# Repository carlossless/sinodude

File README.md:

# sinodude

A programming tool for SinoWealth 8051 microcontrollers.

## Warning

**This tool is experimental. Use at your own risk.**

SinoWealth microcontrollers have limited public documentation. This tool has been developed through reverse engineering and may not work correctly with all chip variants and all configurations.

## Supported Programmers

| Programmer | Description | Notes |
|------------|-------------|-------|
| sinodude-serial | Open-source Arduino Nano (ATmega328P or ATmega328PB) based programmer. See [firmware/README.md](firmware/README.md) for details. | Recommended |
| sinolink | The genuine SinoWealth SinoLink USB dongle (`258a:5063` / `258a:5007`), driven over WinUSB-style vendor control transfers plus bulk endpoints. | See the limitations below |

## Using the SinoLink dongle

Pick the backend with `-c sinolink` and the target power with `--power`:

| `--power` | effect |
|---|---|
| `3v3` (default) | dongle supplies 3.3 V |
| `5v` | dongle supplies 5 V |
| `external` | load switch stays off; the board powers the target |

The selection is checked against the part's `compatible_voltages` and then **verified against the
dongle's ADC**, so asking for 5 V on a 3.3 V-only part is refused and a rail that does not measure
what was asked for is an error rather than a silent overvolt.

```sh
sinodude read     -c sinolink -p sh68f90a --power 3v3 --flash out.hex
sinodude write    -c sinolink -p sh68f90a --power 5v  --flash firmware.hex
sinodude erase    -c sinolink -p sh68f90a --power 3v3
sinodude security -c sinolink -p sh68f90a --power 3v3 --write_protect 3
```

`sinodude sinolink` exposes the dongle directly for diagnostics, below the part abstraction:

```sh
sinodude sinolink probe
sinodude sinolink connect --part sh68f90a --power 3v3
sinodude sinolink dump    --part sh68f90a --power 3v3 --addr 0x1000 --len 0x40 --region custom
sinodude sinolink erase   --part sh68f90a --power 3v3 --erase_mode mass
sinodude sinolink program --part sh68f90a --power 3v3 --bin image.bin --addr 0
sinodude sinolink recover --part sh68f90a --power 3v3   # erase + restore upper options in one session
```

### Limitations

**The per-chip config blob is only solved for SH68F90A.** The dongle latches ChipType, the link
class, geometry and the region addresses from a 1 KiB blob the host downloads at connect. Deriving
that blob from a part's parameters is unfinished, so every other part gets the captured SH68F90A
blob with a handful of fields patched, and the driver warns when that happens. Symptom of a wrong
blob is a read that returns one uniform byte for the whole address space.

**Erased code flash reads `0x00` on SH68F90A, not `0xFF`.** Do not blank-check against `0xFF`.

**Mass erase clears the code options.** It takes the whole part with it, including the boot region
and the custom/option region, so the options have to be written back afterwards. The `write`
subcommand does this for you: it snapshots the custom region before erasing and restores it as part
of the write.

**Program code options with `sinolink options`, never with a raw write.** The code options live in
the custom region, but writing them there with an ordinary program request only sets the bits the
chip lets you set; the rest silently refuse and the operation reports `0xcc`. `bRequest 0x11`
(`sinodude sinolink options`) stages them out of the config blob instead and sets every bit,
including the ones a raw write cannot.

**Result `0xcc` means the write did not verify**, not "transient, retry". The dongle programs, reads
back, and reports `0xcc` on a mismatch. Treat it as a refused write.

**The dongle wedges, and a wedged dongle lies to you.** After enough operations it starts failing
everything: `0x09` on connect, `0xcc` on every write, long chunked reads that disagree between runs.
None of that means the target is broken. Power-cycle the dongle's USB port and it comes back:

```sh
uhubctl -l <hub> -p <port> -a cycle -d 2      # find it with: uhubctl | grep 258a
```

Cycle it before trusting any negative result, and between long write sequences. Several findings in
this file had to be re-verified on a freshly cycled dongle before they could be believed.

**The custom page at `0x1000` holds several different fields; do not write it blind.** On an
SH68F90A the layout is CustomerID at `0x1000`, OperationNumber at `0x1004`, CustomerOption at
`0x1006` and the **security/protection record at `0x100a`**. Writing a 16-byte block at `0x1000`
therefore writes the protection record too. Bytes put there decode as per-group protection: writing
`0f 00 00 88` at `0x100a` marks group 0 protected, which shows up as a program failing at address 1,
and `00 00 00 88` marks groups 6 and 7.

Protection only takes effect with the flag byte `0x33` at record offset `0x10` plus the 6-byte mark,
so stray bits in the record decode as protected without actually blocking writes. Use the
`security` subcommand to check what is really in there.

**Writing the `0x1000` page erases code flash `0x0000-0x0fff`** as a side effect, verified with a
dongle power cycle between write and read. So write custom fields **before** the flash image, never
after. The `write` subcommand already orders it that way.

Mass erase clears the whole page, protection record included, so re-write what you need after any
erase-and-program cycle.

**Do not read immediately after a write.** The dongle answers from a stale internal buffer: a full
dump taken right after an option write returned the option bytes at address 0. The driver settles
for 20 ms after programming and after connecting, which was enough to make repeated full-flash
dumps byte-identical, but a verify pass is still worth doing in a separate session.

### Restore the upper code options in the same session as the erase

Code options are eight bytes: 0-3 at `CustomerOption` (`0x1006` on an SH68F90A) and 4-7 at a fixed
`0x1100`, both in the custom region. Byte 7 holds `OP_ISPSIZE` in its high nibble and
`OP_EEPROMSIZE` in its low nibble, inverse-coded so `8` means "reserve nothing". `SH68F90A.GPT`
gives `[EEPROM] 0`, `[ISPSIZE] 0` and `default_code_options[7] = 0x88`, so the whole 64 KiB is code
flash.

**Mass erase clears that page, and if byte 7 comes back `0x00` the part reserves 8 KiB of ISP plus
4 KiB of EEPROM and refuses to program above `0xd000`.** Erase therefore has to put the upper
options back, and this is the part that bites:

> The upper option page is only writable in the ICP session the erase leaves open. Reconnect first
> and the write fails with `0xcc` and nothing lands, every time. `mass_erase_with_mode` restores
> the options before it reconnects, mirroring `blank_security_and_set_code_option_defaults` in
> sinodude-serial, which is called from inside `mass_erase()` for the same reason.

Symptoms of getting this wrong: programming stops at `0xd000` with `0xcc`, the option page at
`0x1100` refuses writes at offset 3 while offsets 0, 1, 2 and 4 take, and the custom space behaves
oddly because the carve-out is live. All of it clears up once byte 7 reads `0x88`.

Two traps while debugging this. Writing **zeros** "succeeds" anywhere, because the echo of an erased
cell already matches, so a zero-fill probe proves nothing. And a **read taken soon after a write**
can return the dongle's stale buffer, so a program-then-verify inside one session can report success
for a region that was never written; power-cycle the dongle before trusting a negative result.

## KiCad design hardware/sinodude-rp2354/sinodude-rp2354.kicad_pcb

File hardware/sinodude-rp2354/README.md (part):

# sinodude-rp2354

A USB ICP programmer for SinoWealth 8051 microcontrollers, built on an RP2354A.

The target-facing side is switchable between 3.3 V and 5 V, level-translated, and can be
actively discharged, so the host can power-cycle a target cleanly. That matters: SinoWealth
parts only enter ICP mode on a power-on sequence, and a target rail that decays slowly
through its own decoupling will not re-trigger it.

The probe header is pin-compatible with the SinoWealth SinoLink V2.2, so existing cables
and adapters work unchanged.

## Status

| | |
|---|---|
| Schematic | complete — 93 components, ERC clean |
| Sourcing | 88 of 93 parts carry an `LCSC` field; the 5 without are mounting holes and Tag-Connect pads |
| PCB | complete — 64 × 36 mm, two layers, fully routed, DRC clean |

## Sourcing

Every component has a footprint. LCSC part numbers are in an `LCSC` field on each symbol,
picked from the JLCPCB catalogue, preferring Basic/Preferred parts where one exists.

**The same field has to exist on the board's footprints, not only on the symbols.** The
Fabrication Toolkit is a pcbnew plugin: it reads footprint fields and knows nothing about
the schematic. With the field only on the symbols its BOM comes out with an empty
`LCSC Part #` column, JLCPCB falls back to guessing from the comment and footprint, and the
guesses are wrong in the expensive direction — it matched `RESET` to a reset switch and
`USB-C` to a different receptacle, and gave up entirely on the diodes, ferrite, inductor and
DUT header. All 88 footprints carry the field now. If you add a part, put `LCSC` on the
symbol *and* make sure it reaches the board.

### Value fields carry the binding spec

Parts whose datasheet imposes a real constraint spell it out in the Value field, Olimex
style, so the requirement travels with the symbol instead of living only in this README:

```
L1   3.3uH/20%/Isat2.4A/DCR140m/POL      C22,C23  15pF/50V/5%/C0G/C0603
C19  10uF/10V/10%/X5R/C0603              R15      750R/1%/ILIM333mA
C20,C21,C37  4.7uF/16V/10%/X5R/C0603     R21      150R/1%/250mW/R1206
R5   33R/1%/R0603                        F1       750mA/Rmax290mR/F1206
Y1   12MHz/CL10pF/ESR50R/ABM8-272-T3      D4-D9    H5VSD3B/VRWM5V/SOD-323
```

Generic 10 k / 100 nF parts keep plain values — stamping specs on those only fragments the
BOM without protecting anything.

### Core regulator parts, against RP2350 datasheet §6.3.8

The datasheet opens that section with *"this should be placed first on any board design and
these guidelines must be strictly followed"*, and gives hard numbers. What is fitted:

| Requirement | Part | Margin |
|---|---|---|
| L: shielded, 3.3 µH ±20%, DCR ≤ 250 mΩ, I_sat ≥ 1.5 A, polarity-marked | AOTA-B201610S3R3-101-T (`C42411119`) | DCR 140 mΩ max, I_sat 2.4 A min ✓ |
| C_OUT: 4.7 µF ±20%, ESR ≤ 250 mΩ, ESL ≤ 6 nH | C21, 0603 4.7 µF 16 V X5R ±10% (`C19666`) | on 1.1 V, so negligible DC-bias loss |
| C_IN: ≥ 4.7 µF, ESR ≤ 50 mΩ | C19, 0603 **10 µF** 10 V X5R (`C19702`) | 10 µF chosen because a 4.7 µF part derates below the floor at 3.3 V bias |
| Second 4.7 µF on V_OUT at a DVDD pin, away from L1/C21 | C37 (`C19666`) | recommended, not mandatory |

**C37 must not sit beside C21.** Parallel to C_OUT it simply doubles the 4.7 µF the
regulator is compensated for, and it picks up the LX node's switching edges. The datasheet
names DVDD pin 23 (QFN-60) as the place for it, but the escapes fanning north out of pins
21-27 leave no corridor there. C37 therefore sits west of U1 on DVDD pin 39, the same
supply: 4.0 mm from the pin and 12.5 mm of copper away from C21.

The inductor's polarity marking is functional, not cosmetic: the datasheet says leakage field
couples into the LX→L→C_OUT loop and affects the control loop and output voltage, which is
why Raspberry Pi had Abracon make a marked part. L1's footprint puts the dot on pad 1, which
must face VREG_LX.

L1 and C21 can only be deleted by powering DVDD from an external 1.1 V supply, disabling the
on-chip regulator and tying VREG_FB to ground — which costs a whole extra regulator, so it is
not worth it here. VREG_AVDD and VREG_VIN still need power in that case regardless, as they
run the power-on reset and brown-out detector.

**U3 (TPS2114A) is `C118265`, listed but currently at zero stock.** It is orderable rather
than absent, and at $1.92 it is the cheapest of its family. TI lists the part ACTIVE. The
only consequence is scheduling: a zero-stock part cannot come off JLCPCB's shelf for
assembly, so it has to be ordered against LCSC lead time or consigned.

**Do not substitute the TPS2115A for it.** The two share a datasheet and a pinout, and
differ in exactly three ways: current-limit range (0.31–0.75 A vs 0.63–2 A), the ILIM
constant (250 vs 500), and r_DS(on) (120 mΩ vs 84 mΩ). Our 333 mA sits mid-range for the
'2114A and *below the bottom* of the '2115A's, where the datasheet notes the minimum is set
"based on accuracy considerations" — i.e. the limit is not characterised there. Getting
333 mA from a '2115A needs R15 = 1.5 kΩ, outside its range; staying inside its range means
≥630 mA to the target, which breaks the 500 mA USB budget. R15's value is bound to the part
choice, which is why its Value field reads `750R/1%/ILIM333mA`.

Left without an LCSC — neither is a part:

| Ref | Why |
|---|---|
| H1–H4 | mounting holes, drilled features rather than components |
| J2 | Tag-Connect TC2030 is bare pads — the pogo cable touches copper |

Every part that is physically placed on the board has an LCSC number. J1, J4, SW1 and SW2
all resolved to exact matches for the footprints already drawn:

| Ref | Part | LCSC | Note |
|---|---|---|---|
| J1 | GCT USB4105-GF-A-120 | `C5184243` | swapped from the HCTL part, see below |
| J4 | ZHOURI DC3-2.54-10PAL | `C5156674` | right-angle shrouded box header |
| SW1, SW2 | C&K KMR221GLFS | `C72443` | the part the KiCad footprint is named after |

**Watch the DC3 suffix when reordering J4.** The family splits on one letter: `-10PAS` is
`Plugin`, i.e. vertical, and `-10PAL` is `Push-Pull`, i.e. **Right Angle**. Only the PAL
fits `IDC-Header_2x05_P2.54mm_Horizontal`. Ordering the PAS gives you a connector that
physically fits the same holes but points the cable straight up off the board.

**U2 is now an AMS1117-3.3** (`C6186`, Basic, ~1.4 M in stock), not the NCP1117 the RP2350
guide uses — NCP1117 is not stocked at JLCPCB. Same SOT-223 land pattern, same pinout
(1 GND, 2 VO, 3 VI).

One part-choice consequence worth knowing:

- **C27 (10 µF on VTGT) slows supply switching.** The TPS211xA will not connect a supply
  until OUT has fallen within 100 mV of it, so on a 5 V → 3.3 V change VTGT must decay to
  ~3.4 V first. TI notes the fast input-to-input slew "reduces the output voltage hold-up
  capacitance requirement". Q1 is therefore not optional for voltage changes, not just for
  ICP power cycling — or drop C27 to 1–4.7 µF.

### 3D models

Every footprint representing a physical part resolves a 3D model — 88 of the 93. The five
without are the Tag-Connect pad pattern and the four mounting holes, none of which is a
component.

Check it with `kicad-cli pcb export step`, not by eye. A footprint can carry a model in the
library and still have none on the board, because the board keeps its own copy of the
footprint; U1 sat like that for a while, model file present, library entry present, board
instance empty.

`flake.nix` exports `KICAD10_3DMODEL_DIR` — without it none of the stock models resolve at
all, since every footprint references that variable.

Two models are generated locally into `3dmodels/`, because the KiCad library ships neither:

| Model | Why |
|---|---|
| `QFN-60-1EP_7x7mm_P0.4mm_EP3.4x3.4mm.step` | the KiCad 3D library has QFN-52 and QFN-56 in 7×7 but **no QFN-60**, so the RP2354A had no body at all |
| `L_Abracon_AOTA-B201610S_0806_2016Metric.step` | matches the custom inductor footprint |

Both were built in FreeCAD to datasheet nominals — the QFN to RP2350 datasheet Figure 143
(D/E 7 BSC, A 0.85, A1 0.02, A3 0.203 REF, D2/E2 3.40, b 0.18, e 0.400 BSC, L 0.40) and the
inductor to Abracon's 2.00 × 1.60 × 1.00 max. Verified bounding boxes are 7.000 × 7.000 ×
0.850 and 2.000 × 1.600 × 1.000, origin centred, seating plane at z=0.

Each is exported as separate solids so it can carry per-solid STEP colour, using the same
three RGB values the stock KiCad models use (body `0.148/0.145/0.145`, leads and terminals
`0.824/0.820/0.781`, pin-1 and polarity marking `0.691/0.664/0.598`). Without that a
generated model renders flat grey next to every other part on the board.

They are visual and mechanical-fit models, not vendor CAD: lead geometry is nominal and
there is no internal detail. Good enough for enclosure fit and collision checks; if you need
certified geometry, replace them with vendor STEP.

Because a 3D model is attached to a footprint, `QFN-60-…_ThermalVias` is **copied** into
`footprints/sinodude.pretty` with its model path retargeted. Its nine thermal vias are also
widened from 0.5/0.2 mm to 0.6/0.3 mm, which is JLCPCB's minimum drill.

`footprints/sinodude.pretty` holds two more project copies, each because the stock footprint
does not fit this board:

| Footprint | Change |
|---|---|
| `USB_C_Receptacle_GCT_USB4105-xx-A_16P_TopMnt_Horizontal` | the four corner ground pads are 1.00 mm tall instead of 1.15 mm, so they clear the receptacle's own shell holes at a 0.25 mm hole-to-copper rule |
| `IDC-Header_2x05_P2.54mm_Horizontal` | the pin 1 arrow is shortened so it does not sit on R26's pad, and the body outline is clipped at the board edge it overhangs |

Copies do not pick up upstream library fixes. The trade is deliberate: with them, every
footprint on the board matches its library and DRC's library check is silent, so a real
drift will show up.

**J1 moved to the GCT USB4105** (`C5184243`, USB4105-GF-A-**120**, 16P, 4143 in stock). The
HCTL footprint referenced a model the library does not ship. GCT has an identical pad set
(A1 A4–A9 A12, B1 B4–B9 B12, SH), so this was a footprint swap with no schematic change, and
it does have a model. Note the `-120` suffix: the plain `USB4105-GF-A` and `-060` are 12-pin
parts and will not fit.

### Known items

- **The ERC pin matrix allows a bidirectional pin on a power-output net.** U4's unused pins
  (7–10 = A5–A8, 14–17 = B5–B8) are tied to GND, and GND carries a PWR_FLAG, so the stock
  matrix flags "bidirectional pin connected to power output" eight times. The wiring is
  right and KiCad only sees the pin *type*; it cannot know DIR is strapped. Rather than
  carry eight standing warnings, the Bidirectional × Power-output cell is set to "no
  warning" in the project's ERC matrix. ERC is clean; if you add a real bidirectional pin
  to a driven rail, that pair will no longer be caught for you.

  **Why both ports are grounded, not just the A side.** The SN74LVC8T245 datasheet §8.1 says
  *"It is recommended to tie all unused I/Os to GND. The device should not have any floating
  I/Os when changing translation direction"*, and the overview is blunter: *"The input
  circuitry on both A and B ports is always active and must have a logic HIGH or LOW level
  applied to prevent excess ICC and ICCZ."* The input receiver stays powered on a pin even
  while that pin is driven as an output, so a floating B pin still presents a floating CMOS
  input internally and still burns ICC. Every A and B pin is typed `I/O` in the pin table,
  not "output".

  Grounding an output is only safe because **DIR is hardwired to VCCA**, so the A→B direction
  never changes and B5–B8 sit driving low into GND — no contention, no current. If DIR ever
  became firmware-driven, both sides would need series resistors instead of hard ties. There
  is a note on the sheet saying so.
- **Schematic style follows Olimex.** Ten titled blocks, each boxed with dashed graphic lines
  (`polyline` notes lines, the same construct Olimex uses). Related parts sit next to each
  other and are joined with real wires; KiCad power symbols carry every rail; global labels
  are used only for signals that cross from one block to another.
- **`VTGT`, `ADC_AVDD` and `VREG_AVDD` are real power symbols**, not labels. KiCad takes a
  power symbol's net name from its Value field, so these are stock symbols (`power:VCC`,
  `power:+3.3VA`) with the Value overridden. Keep the Value if you copy them.
- **D1 is wired as a pass-through**, not as a shunt with its two I/O1 pins tied together.
  D+/D- enter one side of the USBLC6 and leave the other, so the signal runs through the
  diode pads rather than past them on a stub. That is ST's application circuit and gives the
  clamp a proper current path — but it does mean **D1 cannot be left unpopulated**.
- **`TDA` (header pin 7) is the Andes AICE data wire**, not an 8051 signal. SinoWealth's
  tool-selection note tabulates the adapter signals per target core: ARM gets SWD
  (`VDD SWCLK SWDIO GND`), Andes gets AICE (`VDD TCK TDA GND`), and the 8051 parts get
  `VDD TCK TDI TDO GND`. The 2x5 header carries both styles at once, so TDA shares TCK with
  the 8051 path and is otherwise unused until an Andes-core target is supported. It gets its
  own translator with a live DIR so firmware can drive it either way, and its passives now
  match the other target lines exactly: D9 clamp, 22 R series (R32), 10 k pull-up to `VTGT`
  (R33).

  An earlier revision gave pin 7 a 330 R series resistor and a fitted 100 nF, copied from
  what was taken to be SinoLink's equivalent net. Neither is on SinoLink's TDA: its cap
  position (C28) carries the value `DNI` and is not fitted, and the only 330 R on that sheet
  is a transistor-switched pull-up on **TDO**, a different pin. Together they made a 33 us
  low-pass on a wire whose whole protocol is edge timing. The cap is gone and D9 sits on its
  footprint, which also closes the gap where pin 7 was the only target signal with no clamp.
- **U1 uses the ThermalVias QFN footprint** (vias under the exposed pad). The project copy
  drills them at 0.3 mm rather than the stock 0.2 mm, so they are inside JLCPCB's standard
  capability; if you retarget to a fab with a finer drill there is nothing to change.
- **GPIO17–25 and 27–29 are unused** and carry no-connect flags. They are free if a later
  revision wants a header or a second target interface.
- **Both board edges are cut back from where the footprints put them**, so the connectors
  reach through a case wall. The GCT footprint's `PCB Edge` line on `Dwgs.User` sits flush
  with the receptacle's mating face; the Edge.Cuts line is 1.4 mm inboard of it. J4 gets the
  same treatment at the other end. If you ever move J1 or J4, the edges move with them.
- **F1 is a 750 mA part, not 500 mA.** Worst case through it is U3's target limit plus the
  board's own draw. The limit is not the 333 mA typical: scaling the datasheet's 700 Ω row
  (0.30 / 0.36 / 0.50 A) to R15 = 750 Ω gives **280 / 336 / 467 mA**, so worst case is
  ~540 mA. Against a 500 mA hold that is under 20%
  margin before derating, and PPTC hold current falls with ambient while U2 sits beside it
  burning ~0.7 W at that current, so it would nuisance-trip. The fitted part is now
  Littelfuse `1206L075/16WR` (`C371166`): 750 mA hold, 1.5 A trip, 90 mΩ typical and 290 mΩ
  after a trip, in the same 1206 land. Note the stock — about 6 k against 300 k for the
  500 mA Jinrui part it replaced. F1 guards the host port against a board fault; the
  target's own overcurrent limit is U3, so raising F1 does not weaken that.

  A **TI TPD3S014** (`C87384`, SOT-23-6) was weighed and turned down. It would replace both
  F1 and D1 with one part, limit electronically at a guaranteed 0.67 A rather than tripping
  thermally, and drop 42–56 mV instead of up to 125 mV — but it costs about a dollar more
  per board against two commodity parts, it is an Extended part at JLCPCB, and its 0.5 A
  continuous rating leaves only 14% over our worst case. Glasgow revC3 does use one, with no
  polyfuse at all. Do not reach for the TPD3S**044** if you revisit this: its limit is
  guaranteed only above 1.60 A, so a fault would pull more than a 500 mA host allows before
  it acted.
- **TPS2114A is old but not end-of-life.** TI lists both the TPS2114A and TPS2115A as
  ACTIVE — in production and recommended for new designs. The problem is purely that JLCPCB
  does not carry it, so it is a distributor question, not a lifecycle one: buy it from
  Digi-Key or Mouser and the part is fine.

## Board sections

```
      USB-C          power         RP2354A       translators      DUT 2x5
   ┌──────────┬────────────────┬──────────────┬──────────────┬────────────┐
   │ J1 D1 F1 │ U2 3V3  U3 mux │ U1  Y1  L1   │ U4  U5  U6   │ J4 + 22R   │
   │          │ Q1 discharge   │ SW1 SW2  J2  │              │ + ESD      │
   └──────────┴────────────────┴──────────────┴──────────────┴────────────┘
```

Signal flows left to right. Everything right of the translators is referenced to `VTGT`;
everything left of them is 3.3 V. RP2354 GPIOs are not 5 V tolerant, so no target-facing
signal bypasses a translator.

## DUT header (J4) — SinoLink V2.2 pinout

```
 1 VTGT    2 TCK
 3 GND     4 TDI
 5 GND     6 TMS
 7 TDA     8 TDO / DATA
 9 nRST   10 GND
```

Pin 7 serves Andes-core targets (`VDD TCK TDA GND`); pins 4, 6, 8 and 9 serve the 8051 path
(`TDI TMS TDO nRST`). TCK and VTGT are common to both. The dongle's single-wire pulse-width
transport for 8051 parts runs on **TDO, pin 8**, not on TDA.

### Wire-protocol coverage

SinoLink runs four wire protocols across these ten pins. Every one of them needs the same
three things from the hardware: a driven clock, a line that can turn around, and a reset.

| protocol | target | signals | path here |
|---|---|---|---|
| protoA, JTAG bit-bang | 8051 | nRESET TCK TDI TMS, TDO in | U4 drives the first four, U5 turns TDO around |
| protoB, single-wire pulse-width | 8051 | TCK + one bidirectional data wire | U4 drives TCK, U5 turns pin 8 around |
| CMSIS-DAP SWD | ARM | SWCLK(=TCK) SWDIO(=TDO) nRESET | same pins, U5 turns SWDIO around |
| AICE | Andes | TCK + TDA | U4 drives TCK, U6 turns pin 7 around |

The three lines that have to reverse (TDO, TDA, and nothing else) each sit on their own
translator with a GPIO-controlled DIR. TCK, TDI, TMS and nRST never reverse in any of the
four, so they share U4 with its DIR strapped `A->B`; `XLAT_OE` still tri-states all four so
another probe can drive the header.

**Pull-up strength is the one place SinoLink's topology forces a choice.** It translates its
data wire with a PCA9306, a passive pass-FET that cannot drive high at all, so both sides
need pull-ups and it fits 1 kOhm on the MCU side plus a transistor-switched 330 Ohm on the
target side. Those resistors are its high-side driver, not a bus bias. The SN74LVC1T45 used
here is push-pull and drives high itself, so no switched pull-up is needed; what remains is
the released-line case, where the target drives open-drain and the pull-up alone sets the
rising edge. R31 and R33 are therefore **1 kOhm**, matching SinoLink's static value, for a
~30 ns edge into the ~30 pF a short ribbon presents rather than the ~300 ns a 10 kOhm would
give. R29 on nRST stays 10 kOhm: a reset line is not clocked and should not fight a target
that drives it.

**Target-referenced I/O** (SinoLink's third VREF setting, after 5 V and 3.3 V) needs no
extra parts: leave U3 in its reset state (`D1 = D0 = 1`, OUT Hi-Z), let the target feed pin
1, and `VTGT` — which *is* pin 1 — becomes the target's own rail. That is what the
translators take as VCCB, and `VTGT_SENSE` reads it back on ADC0.

## Target supply (U3, TPS2114A)

Truth table, in the datasheet's own `D1, D0` column order:

| D1 | D0 | OUT | Mode |
|----|----|-----|------|
| 1 | 1 | Hi-Z | **off, the reset default** via R13/R14 10 k pull-ups |
| 1 | 0 | IN1 | 5.0 V |
| 0 | 1 | IN1 or IN2 | auto, picks whichever input is higher |
| 0 | 0 | IN2 | 3.3 V |

Note the pin/bit order: GPIO11 drives D0 and GPIO12 drives D1, so the firmware word is
`(D1 << 1) | D0`. Writing `D1=0, D0=1` gets you auto-switching, not a hard 5 V select.

`STAT` (GPIO14) is a supply-source indicator, not a fault flag. It is open-drain and pulls
low both when IN1 is selected **and** when OUT is Hi-Z, so it only disambiguates against the
mode firmware commanded. It is Hi-Z only while IN2 is selected.

Current limit is `I = 250 / R_ILIM`; R15 = 750 Ω gives 333 mA, which keeps probe plus target
inside a plain USB 500 mA budget. The part is a **TPS2114A**, not the TPS2115A: the '2115A's
specified ILIM adjustment range starts at 0.63 A, so 333 mA is off the bottom of it and the
limit accuracy is unspecified there. The two are pin-, package- and datasheet-identical, and
the '2114A's constant is half, putting 333 mA mid-range.

There is no series Schottky, so the target sees the full rail. Expect roughly 0.2 V below
nominal under load: the polyfuse F1 contributes 0.1 V to 0.4 V depending on the part fitted,
the mux another ~40 mV at 333 mA.

`VTGT` is capped at **5.25 V**, USB 5 V at +5 %. The translators' VCCB abs-max is 5.5 V, but
the binding limit is the ESD suppressors D4–D9: the H5VSD3B is specified to VRWM = 5 V with
VBR(min) = 6.2 V, so above ~5.25 V its leakage is unspecified and the margin to the
breakdown knee gets thin. **An external target above 5.5 V destroys U4–U6.**

## Target discharge (Q1)

`VTGT` is pulled down through R21 (150 Ω, 1206) by Q1. At 5 V that is 167 mW into a 250 mW
part, so it is rated for continuous assertion, but it is meant to be pulsed. R20 (100 k)
holds the gate low so the FET stays off while the RP2354 is in reset and its GPIOs are
inputs.

## Indicators (D2, D3)

Both run from `+3V3` through 470 Ω into the GPIO, so the pin sinks and both are active-low.

**Do not size these by current.** The two LEDs are binned at different test currents, and
reading the LCSC catalogue line instead of the datasheet gets this backwards:

| | part | Iv (bin range) | Vf | at | efficacy |
|---|---|---|---|---|---|
| D2 green, 517 nm | `C7496818` | 160–230 mcd | 2.6–2.9 V | IF = 5 mA | 32–46 mcd/mA |
| D3 red, 625 nm | `C2286` | 145–300 mcd | 1.8–2.4 V | IF = 20 mA | 7.3–15 mcd/mA |

At their respective test points the green is three to four times more efficient per
milliamp, and both are 120° parts, so the mcd figures compare directly for perceived
brightness. That is why the green gets the same resistor as the red rather than a smaller
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
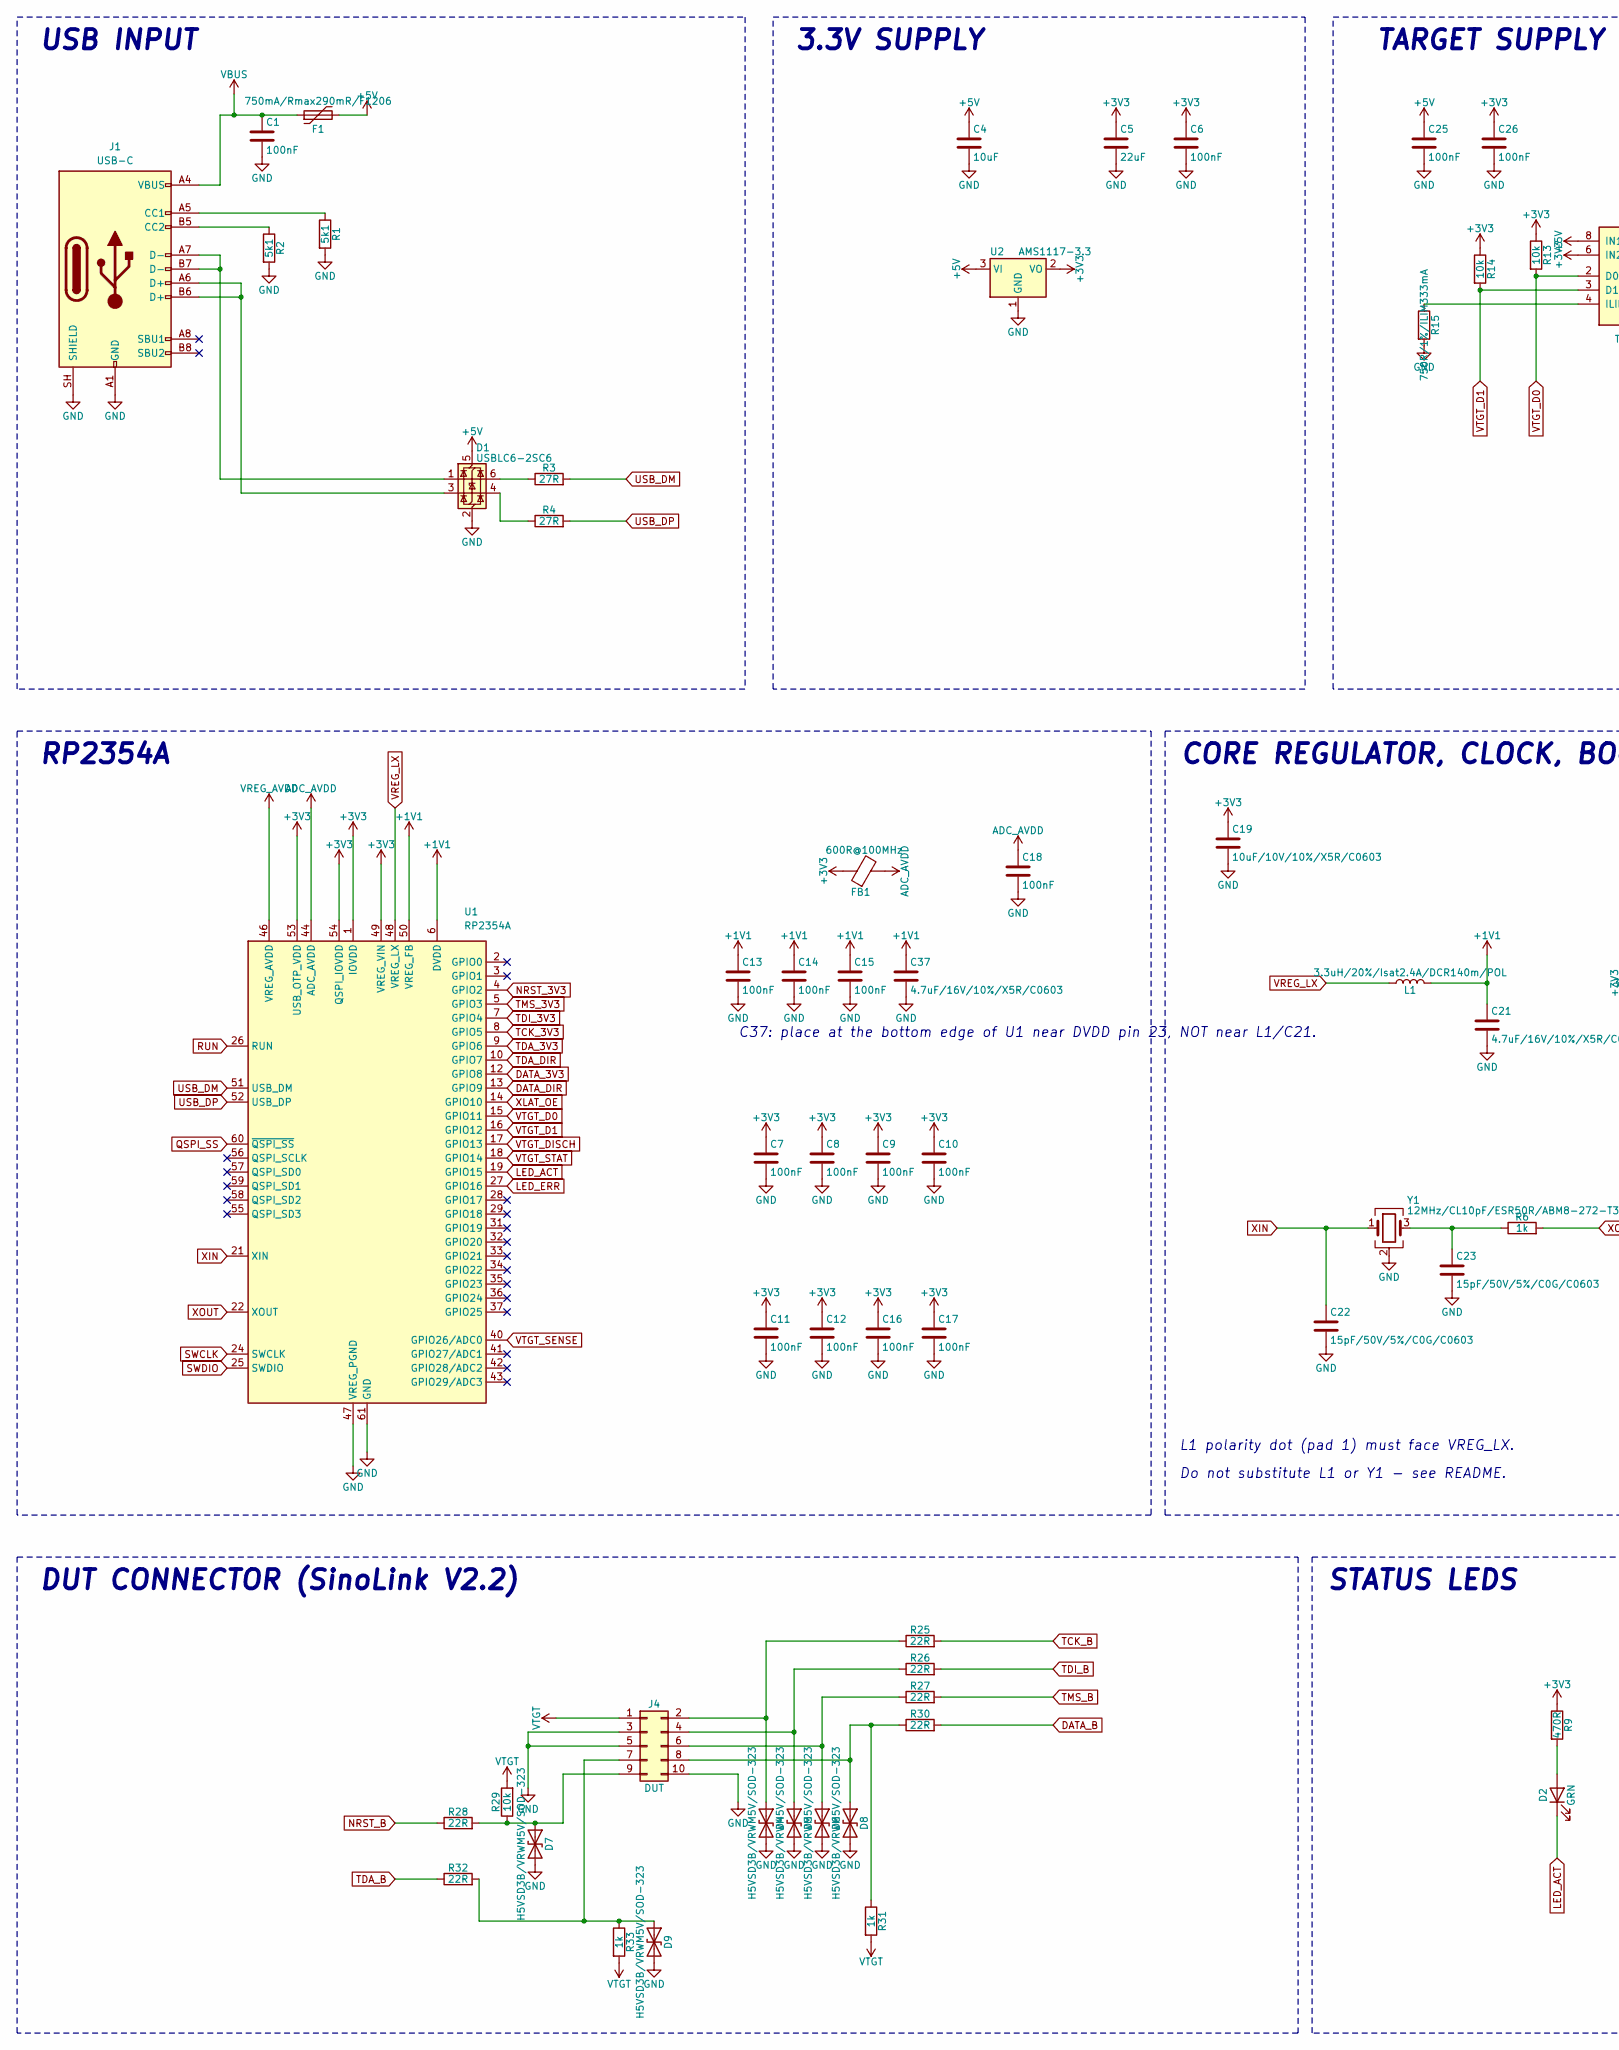
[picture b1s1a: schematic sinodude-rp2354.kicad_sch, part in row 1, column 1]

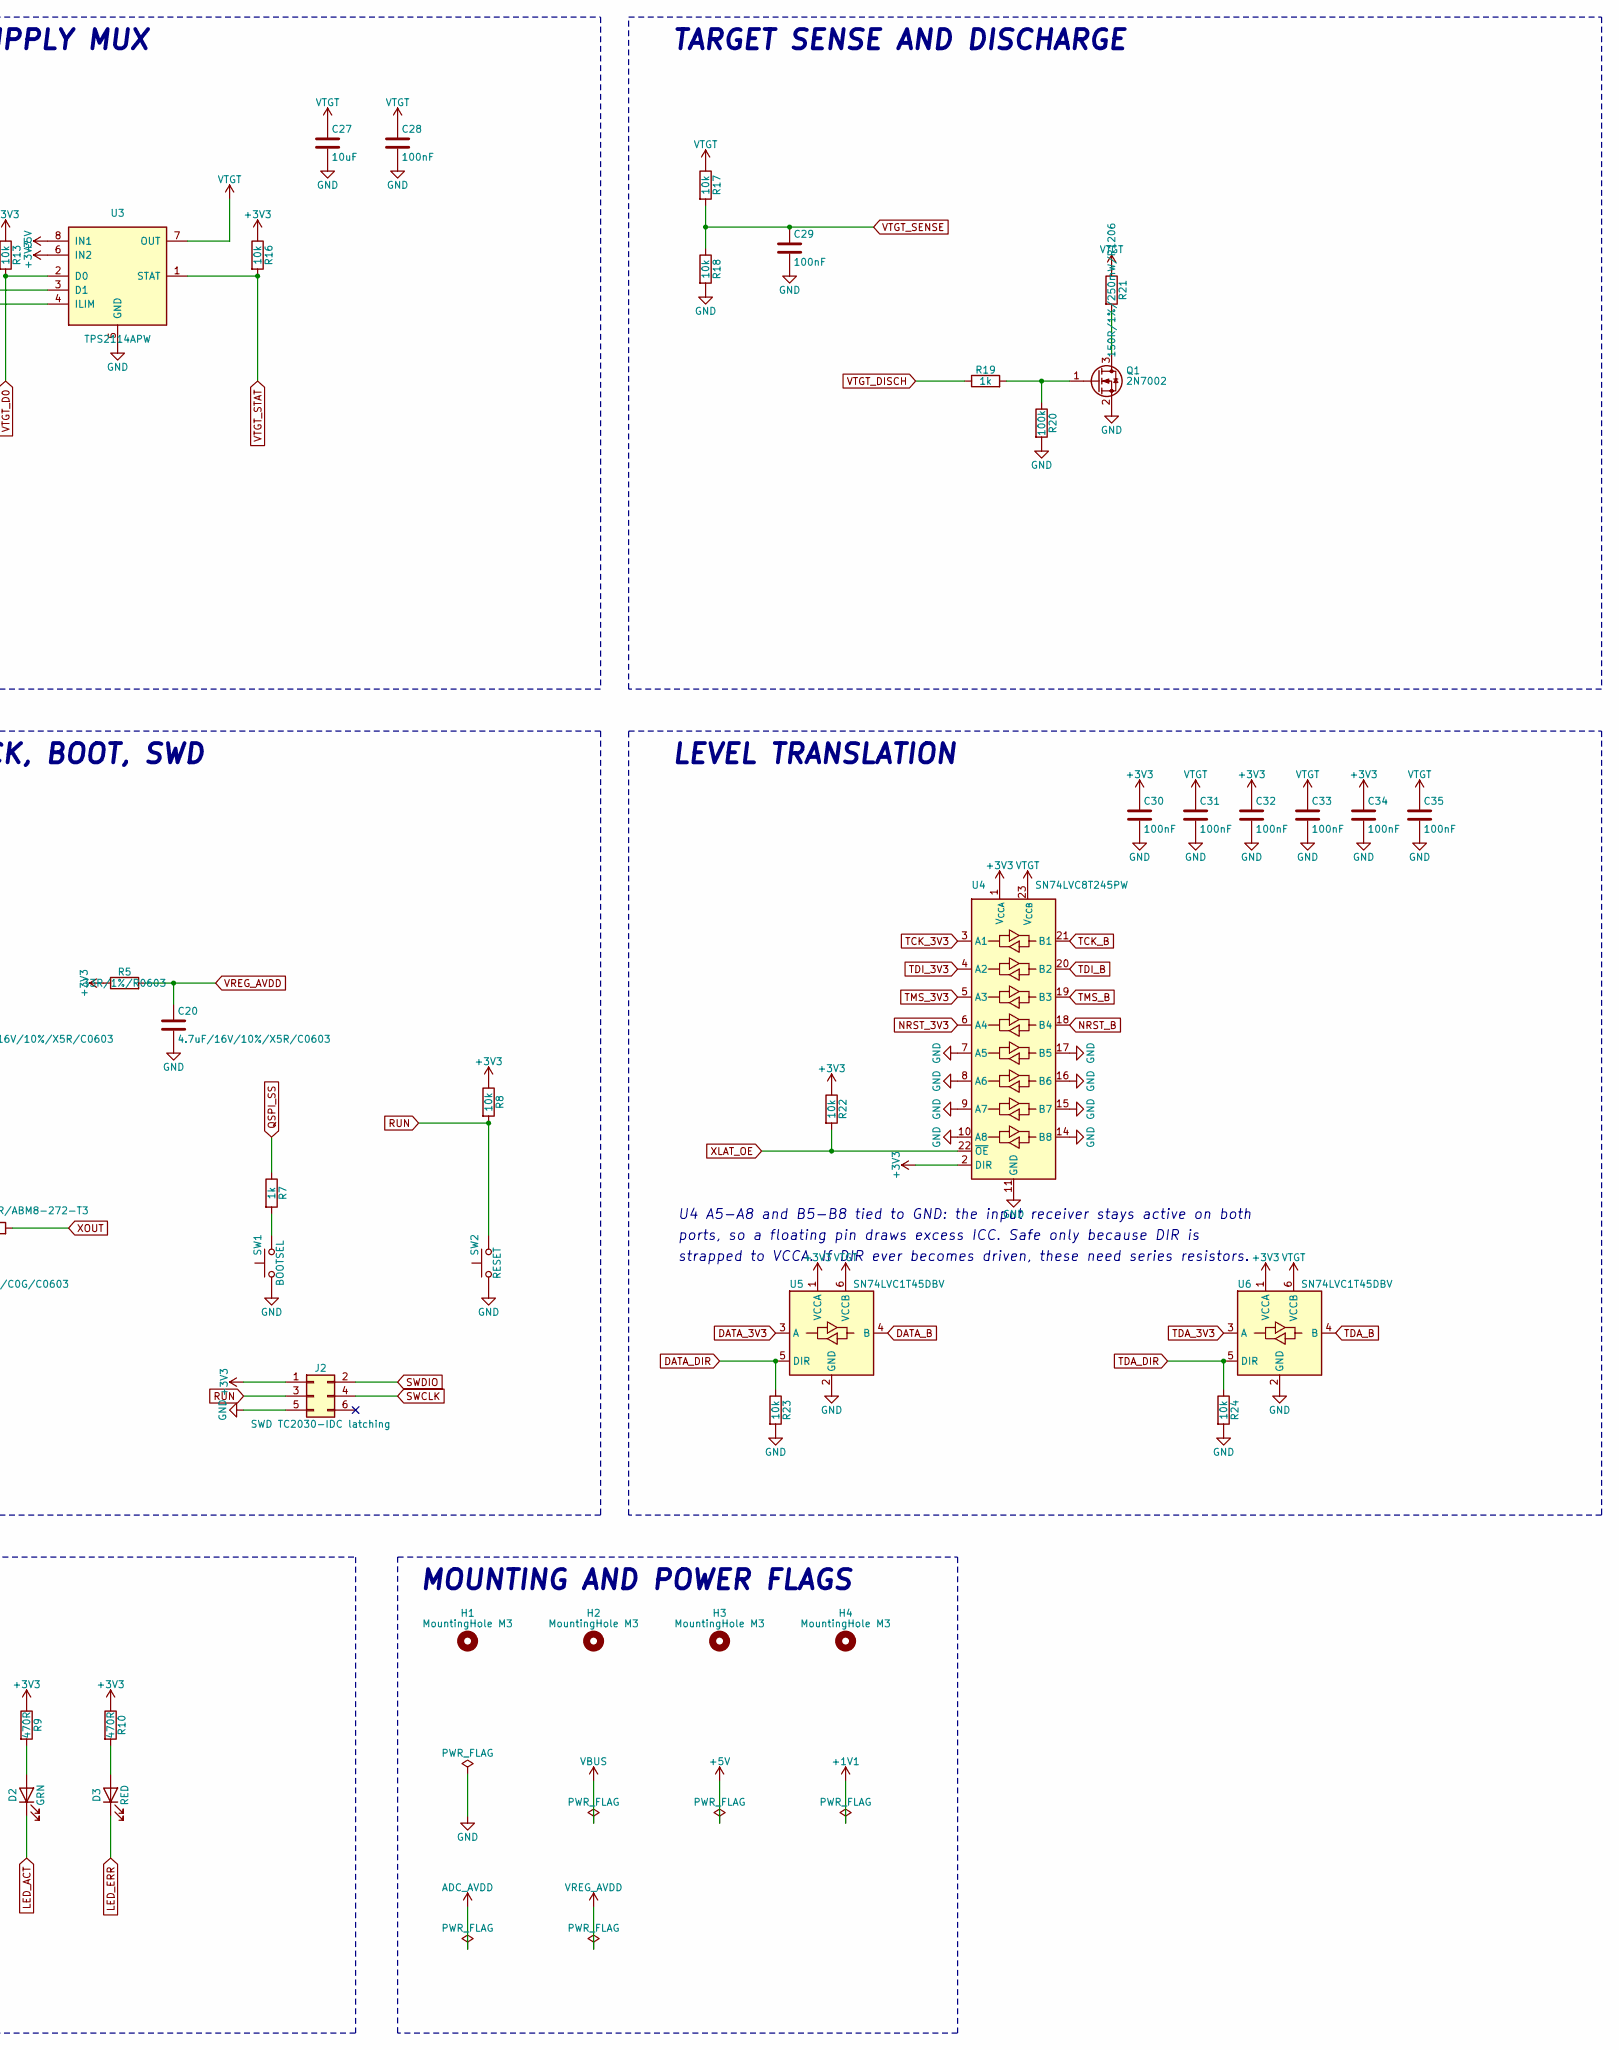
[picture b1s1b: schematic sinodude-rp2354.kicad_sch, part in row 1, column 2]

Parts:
C1, C6, C7, C8, C9, C10, C11, C12, C13, C14, C15, C16, C17, C18, C25, C26, C28, C29, C30, C31, C32, C33, C34, C35: 100nF; C_0603_1608Metric; LCSC C14663
C4, C27: 10uF; C_0805_2012Metric; LCSC C15850
C5: 22uF; C_1206_3216Metric; LCSC C87996
C19: 10uF/10V/10%/X5R/C0603; C_0603_1608Metric; LCSC C19702
C20, C21, C37: 4.7uF/16V/10%/X5R/C0603; C_0603_1608Metric; LCSC C19666
C22, C23: 15pF/50V/5%/C0G/C0603; C_0603_1608Metric; LCSC C1644
D1: USBLC6-2SC6; SOT-23-6; LCSC C2687116
D2: GRN; LED_0603_1608Metric; LCSC C7496818
D3: RED; LED_0603_1608Metric; LCSC C2286
D4, D5, D6, D7, D8, D9: H5VSD3B/VRWM5V/SOD-323; D_SOD-323; LCSC C20615806
F1: 750mA/Rmax290mR/F1206; Fuse_1206_3216Metric; LCSC C371166
FB1: 600R@100MHz; R_0603_1608Metric; LCSC C1002
H1, H2, H3, H4: MountingHole M3; MountingHole_3.2mm_M3
J1: USB-C; USB_C_Receptacle_GCT_USB4105-xx-A_16P_TopMnt_Horizontal; LCSC C5184243
J2: SWD TC2030-IDC latching; Tag-Connect_TC2030-IDC-FP_2x03_P1.27mm_Vertical
J4: DUT; IDC-Header_2x05_P2.54mm_Horizontal; LCSC C5156674
L1: 3.3uH/20%/Isat2.4A/DCR140m/POL; L_Abracon_AOTA-B201610S_0806_2016Metric_Polarized; LCSC C42411119
Q1: 2N7002; SOT-23; LCSC C8545
R1, R2: 5k1; R_0603_1608Metric; LCSC C23186
R3, R4: 27R; R_0603_1608Metric; LCSC C25190
R5: 33R/1%/R0603; R_0603_1608Metric; LCSC C23140
R6, R7, R19, R31, R33: 1k; R_0603_1608Metric; LCSC C21190
R8, R13, R14, R16, R17, R18, R22, R23, R24, R29: 10k; R_0603_1608Metric; LCSC C25804
R9, R10: 470R; R_0603_1608Metric; LCSC C23179
R15: 750R/1%/ILIM333mA; R_0603_1608Metric; LCSC C23241
R20: 100k; R_0603_1608Metric; LCSC C25803
R21: 150R/1%/250mW/R1206; R_1206_3216Metric; LCSC C17917
R25, R26, R27, R28, R30, R32: 22R; R_0603_1608Metric; LCSC C23345
SW1: BOOTSEL; SW_Push_1P1T_NO_CK_KMR2; LCSC C72443
SW2: RESET; SW_Push_1P1T_NO_CK_KMR2; LCSC C72443
U1: RP2354A; QFN-60-1EP_7x7mm_P0.4mm_EP3.4x3.4mm_ThermalVias; LCSC C41378174
U2: AMS1117-3.3; SOT-223-3_TabPin2; LCSC C6186
U3: TPS2114APW; TSSOP-8_4.4x3mm_P0.65mm; LCSC C118265
U4: SN74LVC8T245PW; TSSOP-24_4.4x7.8mm_P0.65mm; LCSC C27643
U5, U6: SN74LVC1T45DBV; SOT-23-6; LCSC C7843
Y1: 12MHz/CL10pF/ESR50R/ABM8-272-T3; Crystal_SMD_3225-4Pin_3.2x2.5mm; LCSC C20625731

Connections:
+1V1: C13.1, C14.1, C15.1, C21.1, C37.1, L1.2, U1.6 (DVDD), U1.23 (DVDD), U1.39 (DVDD), U1.50 (VREG_FB)
+3V3: C5.1, C6.1, C7.1, C8.1, C9.1, C10.1, C11.1, C12.1, C16.1, C17.1, C19.1, C26.1, C30.1, C32.1, C34.1, FB1.1, J2.1, R5.1, R8.1, R9.1, R10.1, R13.1, R14.1, R16.1, R22.1, U1.1 (IOVDD), U1.11 (IOVDD), U1.20 (IOVDD), U1.30 (IOVDD), U1.38 (IOVDD), U1.45 (IOVDD), U1.49 (VREG_VIN), U1.53 (USB_OTP_VDD), U1.54 (QSPI_IOVDD), U2.2 (VO), U3.6 (IN2), U4.1 (V_{CCA}), U4.2 (DIR), U5.1 (VCCA), U6.1 (VCCA)
+5V: C4.1, C25.1, D1.5 (VBUS), F1.2, U2.3 (VI), U3.8 (IN1)
ADC_AVDD: C18.1, FB1.2, U1.44 (ADC_AVDD)
DATA_3V3: U1.12 (GPIO8), U5.3 (A)
DATA_B: R30.2, U5.4 (B)
DATA_DIR: R23.1, U1.13 (GPIO9), U5.5 (DIR)
GND: C1.2, C4.2, C5.2, C6.2, C7.2, C8.2, C9.2, C10.2, C11.2, C12.2, C13.2, C14.2, C15.2, C16.2, C17.2, C18.2, C19.2, C20.2, C21.2, C22.2, C23.2, C25.2, C26.2, C27.2, C28.2, C29.2, C30.2, C31.2, C32.2, C33.2, C34.2, C35.2, C37.2, D1.2 (GND), D4.2 (A2), D5.2 (A2), D6.2 (A2), D7.2 (A2), D8.2 (A2), D9.2 (A2), J1.A1 (GND), J1.A12 (GND), J1.B1 (GND), J1.B12 (GND), J1.SH (SHIELD), J2.5, J4.3, J4.5, J4.10, Q1.2 (S), R1.2, R2.2, R15.2, R18.2, R20.2, R23.2, R24.2, SW1.1, SW2.1, U1.47 (VREG_PGND), U1.61 (GND), U2.1 (GND), U3.5 (GND), U4.7 (A5), U4.8 (A6), U4.9 (A7), U4.10 (A8), U4.11 (GND), U4.12 (GND), U4.13 (GND), U4.14 (B8), U4.15 (B7), U4.16 (B6), U4.17 (B5), U5.2 (GND), U6.2 (GND), Y1.2 (G), Y1.4 (G)
LED_ACT: D2.1 (K), U1.19 (GPIO15)
LED_ERR: D3.1 (K), U1.27 (GPIO16)
NRST_3V3: U1.4 (GPIO2), U4.6 (A4)
NRST_B: R28.1, U4.18 (B4)
unnamed: C23.1, R6.1, Y1.3
unnamed: D1.1 (I/O1), J1.A7 (D-), J1.B7 (D-)
unnamed: D1.6 (I/O1), R3.1
unnamed: D1.3 (I/O2), J1.A6 (D+), J1.B6 (D+)
unnamed: D1.4 (I/O2), R4.1
unnamed: D2.2 (A), R9.2
unnamed: D3.2 (A), R10.2
unnamed: D4.1 (A1), J4.2, R25.1
unnamed: D5.1 (A1), J4.4, R26.1
unnamed: D6.1 (A1), J4.6, R27.1
unnamed: D7.1 (A1), J4.9, R28.2, R29.1
unnamed: D8.1 (A1), J4.8, R30.1, R31.1
unnamed: D9.1 (A1), J4.7, R32.2, R33.1
unnamed: J1.A5 (CC1), R1.1
unnamed: J1.B5 (CC2), R2.1
unnamed: Q1.3 (D), R21.2
unnamed: Q1.1 (G), R19.2, R20.1
unnamed: R7.2, SW1.2
unnamed: R15.1, U3.4 (ILIM)
QSPI_SS: R7.1, U1.60 (~QSPI_SS)
RUN: J2.3, R8.2, SW2.2, U1.26 (RUN)
SWCLK: J2.4, U1.24 (SWCLK)
SWDIO: J2.2, U1.25 (SWDIO)
TCK_3V3: U1.8 (GPIO5), U4.3 (A1)
TCK_B: R25.2, U4.21 (B1)
TDA_3V3: U1.9 (GPIO6), U6.3 (A)
TDA_B: R32.1, U6.4 (B)
TDA_DIR: R24.1, U1.10 (GPIO7), U6.5 (DIR)
TDI_3V3: U1.7 (GPIO4), U4.4 (A2)
TDI_B: R26.2, U4.20 (B2)
TMS_3V3: U1.5 (GPIO3), U4.5 (A3)
TMS_B: R27.2, U4.19 (B3)
USB_DM: R3.2, U1.51 (USB_DM)
USB_DP: R4.2, U1.52 (USB_DP)
VBUS: C1.1, F1.1, J1.A4 (VBUS), J1.A9 (VBUS), J1.B4 (VBUS), J1.B9 (VBUS)
VREG_AVDD: C20.1, R5.2, U1.46 (VREG_AVDD)
VREG_LX: L1.1, U1.48 (VREG_LX)
VTGT: C27.1, C28.1, C31.1, C33.1, C35.1, J4.1, R17.1, R21.1, R29.2, R31.2, R33.2, U3.7 (OUT), U4.23 (V_{CCB}), U4.24 (V_{CCB}), U5.6 (VCCB), U6.6 (VCCB)
VTGT_D0: R13.2, U1.15 (GPIO11), U3.2 (D0)
VTGT_D1: R14.2, U1.16 (GPIO12), U3.3 (D1)
VTGT_DISCH: R19.1, U1.17 (GPIO13)
VTGT_SENSE: C29.1, R17.2, R18.1, U1.40 (GPIO26/ADC0)
VTGT_STAT: R16.2, U1.18 (GPIO14), U3.1 (STAT)
XIN: C22.1, U1.21 (XIN), Y1.1
XLAT_OE: R22.2, U1.14 (GPIO10), U4.22 (~OE)
XOUT: R6.2, U1.22 (XOUT)

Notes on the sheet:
USB INPUT
3.3V SUPPLY
C37: place at the bottom edge of U1 near DVDD pin 23, NOT near L1/C21.
DUT CONNECTOR (SinoLink V2.2)
TARGET SENSE AND DISCHARGE
U4 A5-A8 and B5-B8 tied to GND: the input receiver stays active on both
RP2354A
L1 polarity dot (pad 1) must face VREG_LX.
strapped to VCCA. If DIR ever becomes driven, these need series resistors.
ports, so a floating pin draws excess ICC. Safe only because DIR is
Do not substitute L1 or Y1 - see README.
MOUNTING AND POWER FLAGS
TARGET SUPPLY MUX
CORE REGULATOR, CLOCK, BOOT, SWD
LEVEL TRANSLATION
STATUS LEDS

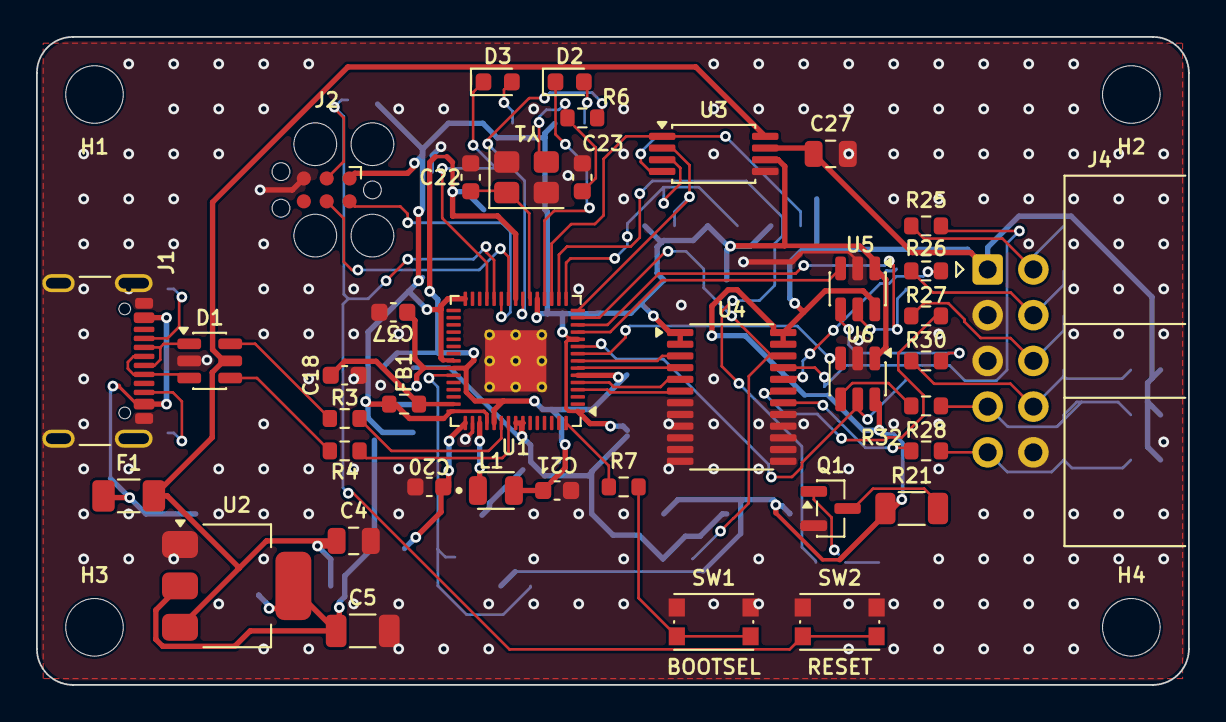
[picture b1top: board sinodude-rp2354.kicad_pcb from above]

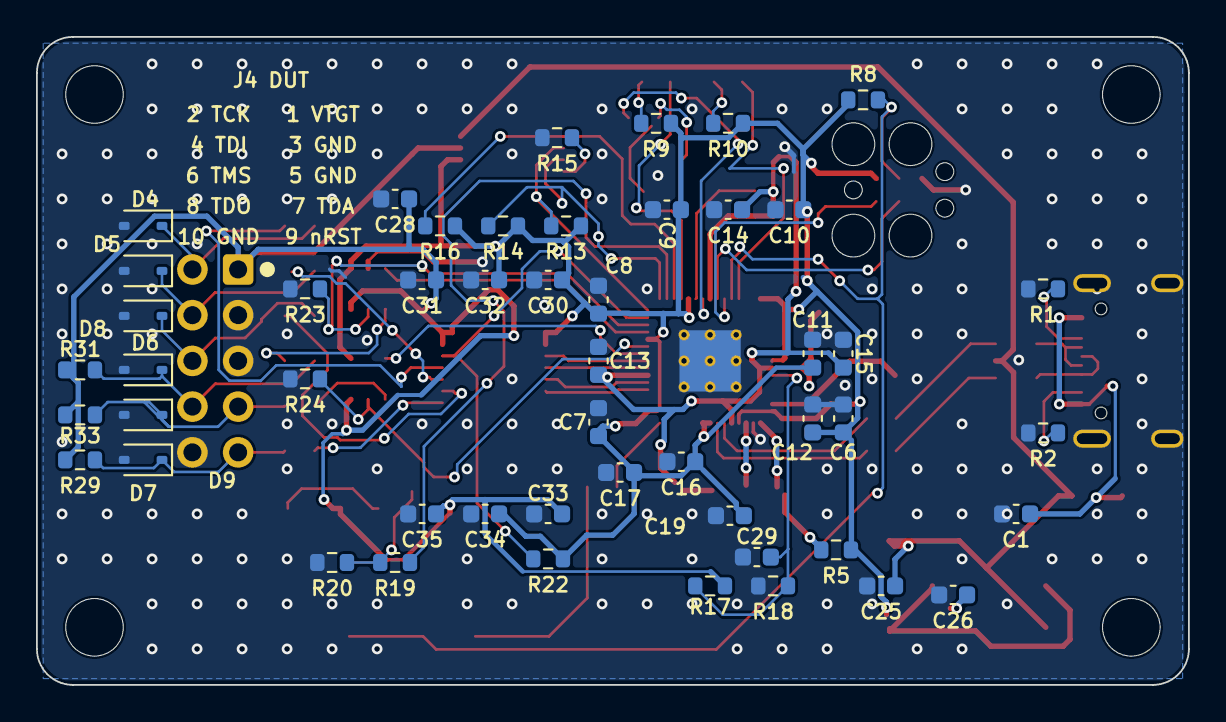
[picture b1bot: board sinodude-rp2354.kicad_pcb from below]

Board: 2 copper layers, 64.0 x 36.0 mm, 93 parts (50 on the bottom side), 58 nets.

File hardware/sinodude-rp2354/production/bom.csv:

Designator,Footprint,Quantity,Value,LCSC Part #
"C1, C10, C11, C12, C13, C14, C15, C16, C17, C18, C25, C26, C28, C29, C30, C31, C32, C33, C34, C35, C6, C7, C8, C9",0603,24,100nF,C14663
C19,0603,1,10uF/10V/10%/X5R/C0603,C19702
"C20, C21, C37",0603,3,4.7uF/16V/10%/X5R/C0603,C19666
"C22, C23",0603,2,15pF/50V/5%/C0G/C0603,C1644
"C27, C4",0805,2,10uF,C15850
C5,1206,1,22uF,C87996
D1,SOT-23-6,1,USBLC6-2SC6,C2687116
D2,0603,1,GRN,C7496818
D3,0603,1,RED,C2286
"D4, D5, D6, D7, D8, D9",D_SOD-323,6,H5VSD3B/VRWM5V/SOD-323,C20615806
F1,1206,1,750mA/Rmax290mR/F1206,C371166
FB1,0603,1,600R@100MHz,C1002
J1,USB_C_Receptacle_GCT_USB4105-xx-A_16P_TopMnt_Horizontal,1,USB-C,C5184243
J4,IDC-Header_2x05_P2.54mm_Horizontal,1,DUT,C5156674
L1,L_Abracon_AOTA-B201610S_0806_2016Metric_Polarized,1,3.3uH/20%/Isat2.4A/DCR140m/POL,C42411119
Q1,SOT-23,1,2N7002,C8545
"R1, R2",0603,2,5k1,C23186
"R10, R9",0603,2,470R,C23179
"R13, R14, R16, R17, R18, R22, R23, R24, R29, R8",0603,10,10k,C25804
R15,0603,1,750R/1%/ILIM333mA,C23241
"R19, R31, R33, R6, R7",0603,5,1k,C21190
R20,0603,1,100k,C25803
R21,1206,1,150R/1%/250mW/R1206,C17917
"R25, R26, R27, R28, R30, R32",0603,6,22R,C23345
"R3, R4",0603,2,27R,C25190
R5,0603,1,33R/1%/R0603,C23140
SW1,SW_Push_1P1T_NO_CK_KMR2,1,BOOTSEL,C72443
SW2,SW_Push_1P1T_NO_CK_KMR2,1,RESET,C72443
U1,QFN-60-1EP_7x7mm_P0.4mm_EP3.4x3.4mm_ThermalVias,1,RP2354A,C41378174
U2,SOT-223-3_TabPin2,1,AMS1117-3.3,C6186
U3,TSSOP-8_4.4x3mm_P0.65mm,1,TPS2114APW,C118265
U4,TSSOP-24_4.4x7.8mm_P0.65mm,1,SN74LVC8T245PW,C27643
"U5, U6",SOT-23-6,2,SN74LVC1T45DBV,C7843
Y1,Crystal_SMD_3225-4Pin_3.2x2.5mm,1,12MHz/CL10pF/ESR50R/ABM8-272-T3,C20625731

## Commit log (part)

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2023-03-08 janky working reading
2023-03-10 rudimentary cli interface
2023-03-10 added documentation to config payload
2023-03-11 more documentation and a GPT file decoding helper
2023-03-11 basic github actions
2023-03-12 some work towards chip configurability
2023-03-24 reorganisation
2023-03-26 broken keyboard flash update driver
2023-03-26 seemly working keyboard flasher
2023-03-26 cleaned up the interface
2023-03-31 wip tidying up keyboard code
2023-03-31 confirmed the booloader gets the right firmware
2023-03-31 more cleanup
2023-04-10 moved out keyboard and crc out of this tool
2024-01-15 flake setup, rustfmt, config update
2024-01-16 partially working writing
2024-01-16 update package name
2024-01-16 import update
2024-10-25 nusb move (macos broken, other platforms untested), flake update
2024-10-26 working and api a bit cleaned up
2025-02-23 ignore result, flake update, nusb update
2025-05-04 set configuration when required
2025-05-04 weirly doesnt work anymore
2025-12-29 deps update, read seems working, write is broken
2026-01-01 partially working serial programming firmware
2026-01-01 sinodude ee
2026-01-02 working setup to launch into programming mode with a p-channel mosfet
2026-01-03 not-working partial jtag-get id
2026-01-03 fetching part_number, but only when not entering jtag mode before
2026-01-03 working reading part_number, code_options
2026-01-03 icp read working
2026-01-04 confirmed working write
2026-01-04 refactoring
2026-01-04 version check
2026-01-04 refactoring and id and part mismatch fix
2026-01-04 progress bars
2026-01-04 gpt decrypt fix
2026-01-04 some initial 68f881 config
2026-01-04 install libudev
2026-01-04 update artifact
2026-01-04 new artifact options
2026-01-04 also build firmware
2026-01-04 add avr-libc
2026-01-04 include firmware
2026-01-04 license, readme updates
2026-01-05 reuse read_chunk
2026-01-06 category cleanup
2026-01-06 cleanup
2026-01-06 decap
2026-01-08 part generation
2026-01-12 working parts and part generation
2026-01-12 readme cleanup and serial operation reordering
2026-01-12 sigint handling
2026-01-12 cargo fmt
2026-01-12 parts generation fixup
2026-01-12 compiling for atmega328pb also
2026-01-12 use nix for most of ci
2026-01-16 mass-erase and security levels
2026-01-17 fixed custom region writting
2026-01-17 correctly check for success signals
2026-01-17 fix double writing the same byte twice
2026-01-17 verify
2026-01-17 reorder commands
2026-01-17 writting and erasing sectors only
2026-01-18 trying custom region write to work
2026-01-18 more experimentation
2026-01-18 back to working state
2026-01-18 invalid code-option recovery, faster reads and writes
2026-01-18 readme update
2026-01-24 generic security handling, part suggestions, part updates
2026-01-24 include all decoded parts
2026-01-24 format
2026-01-25 remove sinolink from the supported programmers
2026-02-01 voltages
2026-02-16 docs: add SH68F90 recovery workflow and detailed troubleshooting
2026-02-16 firmware: bump avr-device to 0.8 to fix broken tiny image
2026-02-17 firmware: bump avr-device to 0.8 to fix broken tiny image (#3)
2026-05-31 decrypt by uknown files by brute forcing it (it's cheap)
2026-05-31 include more decoded parts

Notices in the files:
hardware/sinodude-rp2354/sinodude-rp2354.kicad_pcb:
GPL-3.0-or-later
